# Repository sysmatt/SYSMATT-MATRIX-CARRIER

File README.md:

# SYSMATT-MATRIX-CARRIER
## An all-pcb combined ESB32 based WS2812B matrix carrier and diffuser.

### ... It's a sandwich. 

If you end up building these, please tag me on social media... @SYSMATT on X/Twitter - TY!

These cheap pre-made WS2812B flexible matrix boards are plentiful and availible on Amazon/Aliexpress/etc.  

They look great through a 1mm FR4 PCB diffuser. 

In this repo is the carrier board I created to control them with the common 30pin or 38pin ESP32 WROOM modules.  

It supports WLED easily, and even has suport for audio reactive WLED using the common 6-pin INMP441 digital microphone modules.

The boards are assembled in a sandwich,  The main electronics PCB with the ESP module, Mic module, A SN74AHCT125N used as a voltage translator, and an assortment of connector options for input/output.

The boards can be assembled "smart" (With an ESP) ... or "dumb"... where it will be chained from a smart board. 

Four ESP outputs are voltage level translated in total to allow you to create large matrix displays. 

There is also a fuse.  Because house fires are no joke. 

Designed using through hole because I have a pile of parts (Im a parts hoarder) ... And the are super easy for most people. 

I will add more here when I have time.  There are videos on the PHOTOS-VIDEOS directory.  Also on youtube:

Video link to YouTube:

https://youtube.com/shorts/75FGs6rpeio

https://youtube.com/shorts/8wDof0Con4Y

https://youtube.com/shorts/0d_V_7tXByc

https://www.youtube.com/watch?v=TLycWf7s_p8

I just use a couplle dots of silicone to hold the sandwitch together

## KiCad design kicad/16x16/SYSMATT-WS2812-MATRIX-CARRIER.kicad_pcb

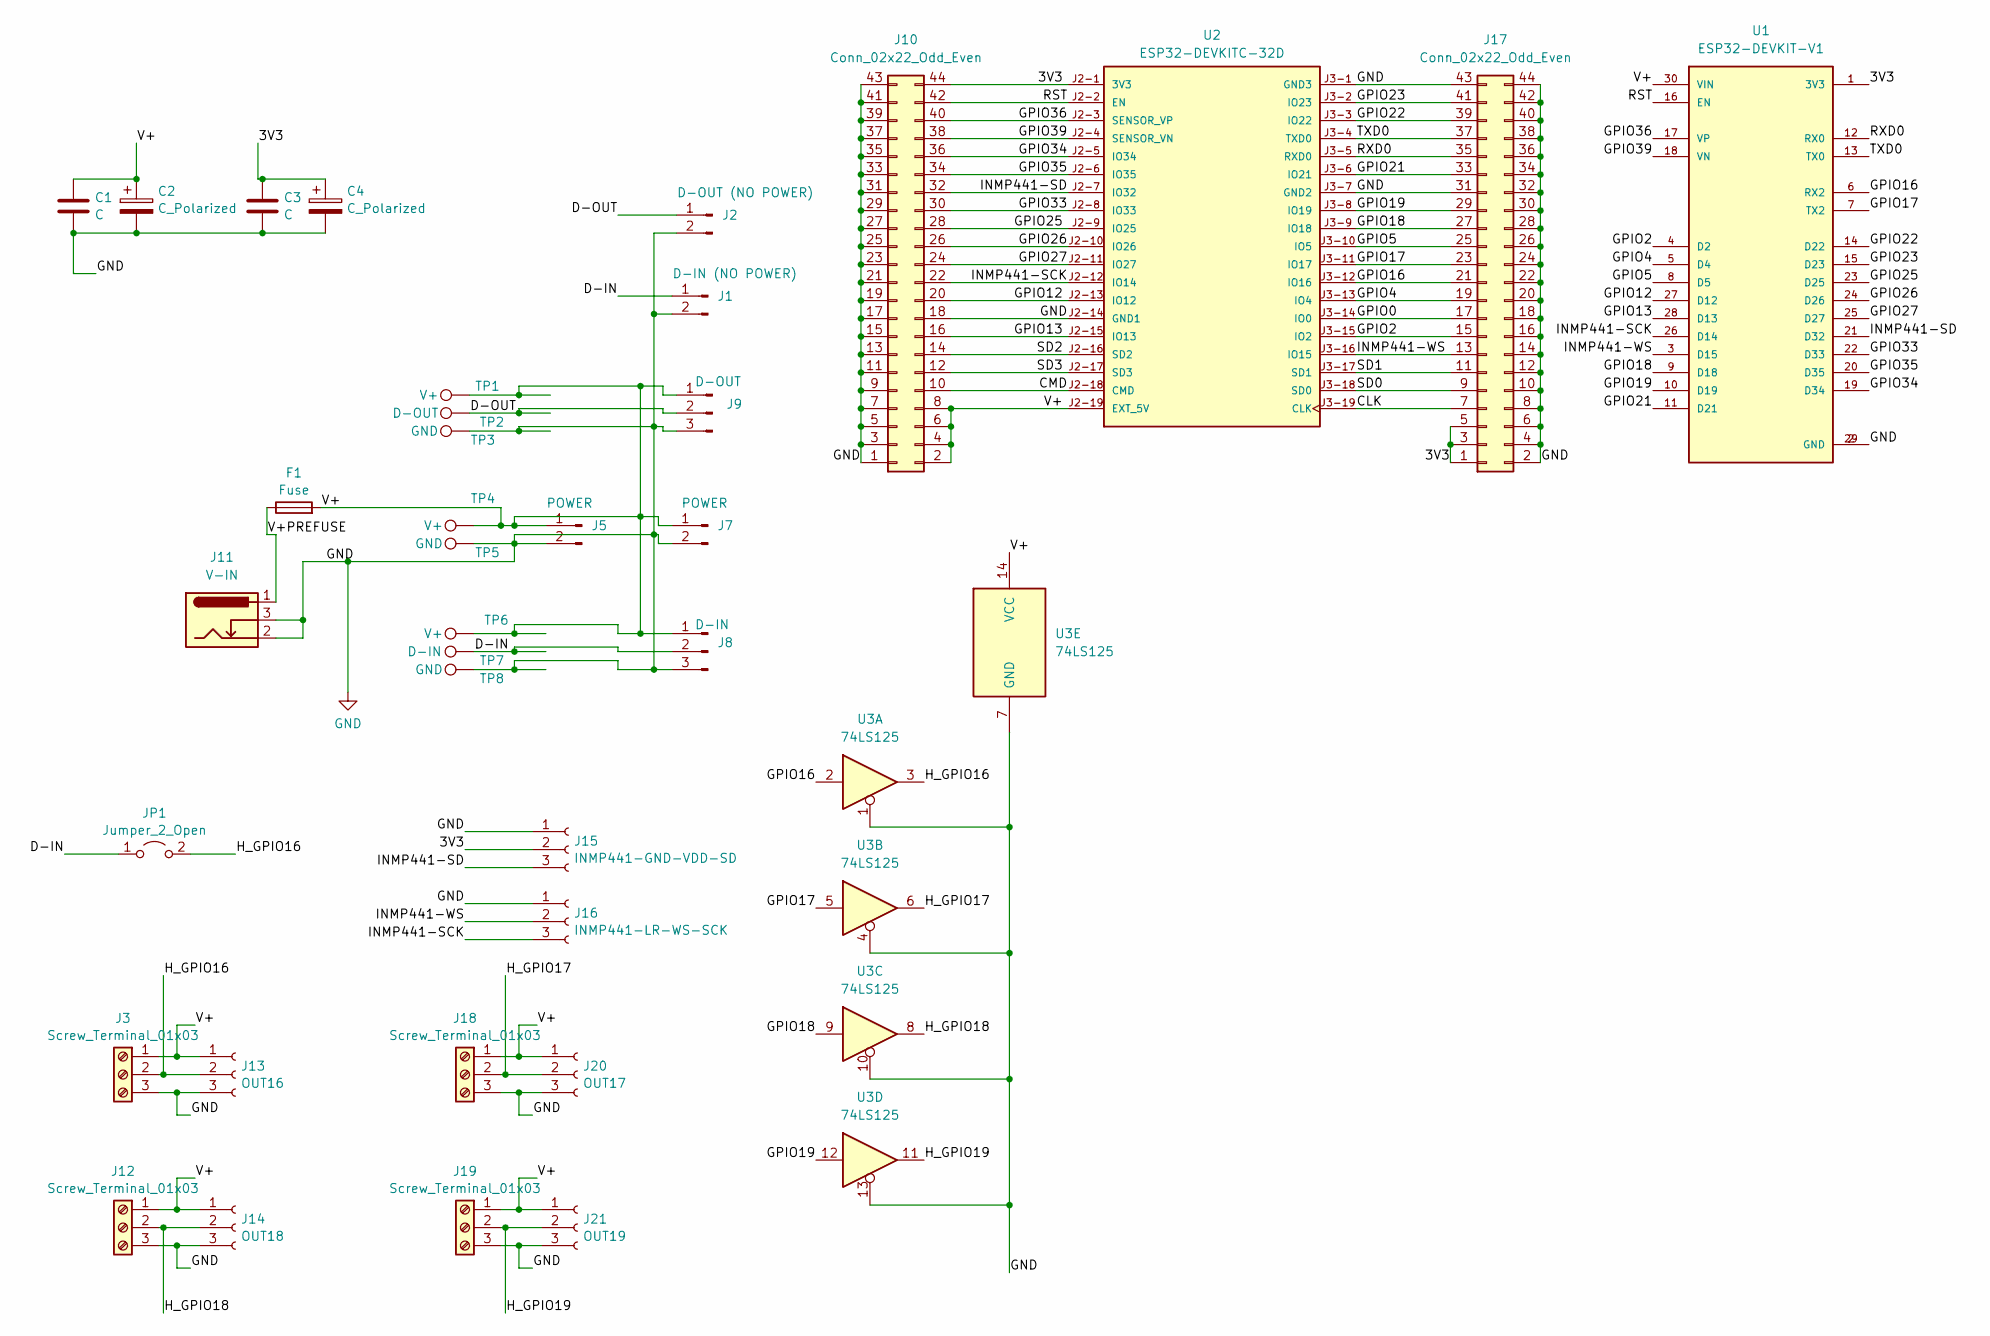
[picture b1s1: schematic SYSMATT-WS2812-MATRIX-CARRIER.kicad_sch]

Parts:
C1, C3: C; C_Disc_D3.8mm_W2.6mm_P2.50mm
C2, C4: C_Polarized; CP_Radial_D6.3mm_P2.50mm
F1: Fuse; Ebay-Fuse-holder-04mmX15mm-black-auto-fuse-dingus
J1: D-IN (NO POWER); PinHeader_1x02_P2.54mm_Horizontal
J2: D-OUT (NO POWER); PinHeader_1x02_P2.54mm_Horizontal
J3, J12, J18, J19: Screw_Terminal_01x03; TerminalBlock_bornier-3_P5.08mm
J5, J7: POWER; PinHeader_1x02_P2.54mm_Horizontal
J8: D-IN; PinHeader_1x03_P2.54mm_Horizontal
J9: D-OUT; PinHeader_1x03_P2.54mm_Horizontal
J10, J17: Conn_02x22_Odd_Even; PinSocket_2x22_P2.54mm_Vertical
J11: V-IN; BarrelJack_Horizontal
J13: OUT16; PinSocket_1x03_P2.54mm_Vertical
J14: OUT18; PinSocket_1x03_P2.54mm_Vertical
J15: INMP441-GND-VDD-SD; PinSocket_1x03_P2.54mm_Vertical
J16: INMP441-LR-WS-SCK; PinSocket_1x03_P2.54mm_Vertical
J20: OUT17; PinSocket_1x03_P2.54mm_Vertical
J21: OUT19; PinSocket_1x03_P2.54mm_Vertical
JP1: Jumper_2_Open; SolderJumper-2_P1.3mm_Open_TrianglePad1.0x1.5mm
TP1, TP4, TP6: V+; TestPoint_Pad_3.0x3.0mm
TP2: D-OUT; TestPoint_Pad_3.0x3.0mm
TP3, TP5, TP8: GND; TestPoint_Pad_3.0x3.0mm
TP7: D-IN; TestPoint_Pad_3.0x3.0mm
U1: ESP32-DEVKIT-V1; MODULE_ESP32_DEVKIT_V1-no-ant-keepout; PARTREV N/A
U2: ESP32-DEVKITC-32D; MODULE_ESP32-DEVKITC-32D-CORRECTED-WIDTH-NARROW; PARTREV V4
U3: 74LS125; DIP-14_W7.62mm_Socket_LongPads

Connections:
/3V3: C3.1, C4.1, J10.44, J15.2, J17.1, J17.3, J17.5, U1.1 (3V3), U2.J2-1 (3V3)
/CLK: J17.7, U2.J3-19 (CLK)
/CMD: J10.10, U2.J2-18 (CMD)
/D-IN: J1.1, J8.2, JP1.1 (A), TP7.1
/D-OUT: J2.1, J9.2, TP2.1
/GPIO0: J17.17, U2.J3-14 (IO0)
/GPIO2: J17.15, U1.4 (D2), U2.J3-15 (IO2)
/GPIO4: J17.19, U1.5 (D4), U2.J3-13 (IO4)
/GPIO5: J17.25, U1.8 (D5), U2.J3-10 (IO5)
/GPIO12: J10.20, U1.27 (D12), U2.J2-13 (IO12)
/GPIO13: J10.16, U1.28 (D13), U2.J2-15 (IO13)
/GPIO16: J17.21, U1.6 (RX2), U2.J3-12 (IO16), U3.2
/GPIO17: J17.23, U1.7 (TX2), U2.J3-11 (IO17), U3.5
/GPIO18: J17.27, U1.9 (D18), U2.J3-9 (IO18), U3.9
/GPIO19: J17.29, U1.10 (D19), U2.J3-8 (IO19), U3.12
/GPIO21: J17.33, U1.11 (D21), U2.J3-6 (IO21)
/GPIO22: J17.39, U1.14 (D22), U2.J3-3 (IO22)
/GPIO23: J17.41, U1.15 (D23), U2.J3-2 (IO23)
/GPIO25: J10.28, U1.23 (D25), U2.J2-9 (IO25)
/GPIO26: J10.26, U1.24 (D26), U2.J2-10 (IO26)
/GPIO27: J10.24, U1.25 (D27), U2.J2-11 (IO27)
/GPIO33: J10.30, U1.22 (D33), U2.J2-8 (IO33)
/GPIO34: J10.36, U1.19 (D34), U2.J2-5 (IO34)
/GPIO35: J10.34, U1.20 (D35), U2.J2-6 (IO35)
/GPIO36: J10.40, U1.17 (VP), U2.J2-3 (SENSOR_VP)
/GPIO39: J10.38, U1.18 (VN), U2.J2-4 (SENSOR_VN)
/H_GPIO16: J3.2, J13.2, JP1.2 (B), U3.3
/H_GPIO17: J18.2, J20.2, U3.6
/H_GPIO18: J12.2, J14.2, U3.8
/H_GPIO19: J19.2, J21.2, U3.11
/INMP441-SCK: J10.22, J16.3, U1.26 (D14), U2.J2-12 (IO14)
/INMP441-SD: J10.32, J15.3, U1.21 (D32), U2.J2-7 (IO32)
/INMP441-WS: J16.2, J17.13, U1.3 (D15), U2.J3-16 (IO15)
/RST: J10.42, U1.16 (EN), U2.J2-2 (EN)
/RXD0: J17.35, U1.12 (RX0), U2.J3-5 (RXD0)
/SD0: J17.9, U2.J3-18 (SD0)
/SD1: J17.11, U2.J3-17 (SD1)
/SD2: J10.14, U2.J2-16 (SD2)
/SD3: J10.12, U2.J2-17 (SD3)
/TXD0: J17.37, U1.13 (TX0), U2.J3-4 (TXD0)
/V+: C1.1, C2.1, F1.2, J3.1, J5.1, J7.1, J8.1, J9.1, J10.2, J10.4, J10.6, J10.8, J12.1, J13.1, J14.1, J18.1, J19.1, J20.1, J21.1, TP1.1, TP4.1, TP6.1, U1.30 (VIN), U2.J2-19 (EXT_5V), U3.14 (VCC)
/V+PREFUSE: F1.1, J11.1
GND: C1.2, C2.2, C3.2, C4.2, J1.2, J2.2, J3.3, J5.2, J7.2, J8.3, J9.3, J10.1, J10.3, J10.5, J10.7, J10.9, J10.11, J10.13, J10.15, J10.17, J10.18, J10.19, J10.21, J10.23, J10.25, J10.27, J10.29, J10.31, J10.33, J10.35, J10.37, J10.39, J10.41, J10.43, J11.2, J11.3, J12.3, J13.3, J14.3, J15.1, J16.1, J17.2, J17.4, J17.6, J17.8, J17.10, J17.12, J17.14, J17.16, J17.18, J17.20, J17.22, J17.24, J17.26, J17.28, J17.30, J17.31, J17.32, J17.34, J17.36, J17.38, J17.40, J17.42, J17.43, J17.44, J18.3, J19.3, J20.3, J21.3, TP3.1, TP5.1, TP8.1, U1.2 (GND), U1.29 (GND), U2.J2-14 (GND1), U2.J3-1 (GND3), U2.J3-7 (GND2), U3.1, U3.4, U3.7 (GND), U3.10, U3.13

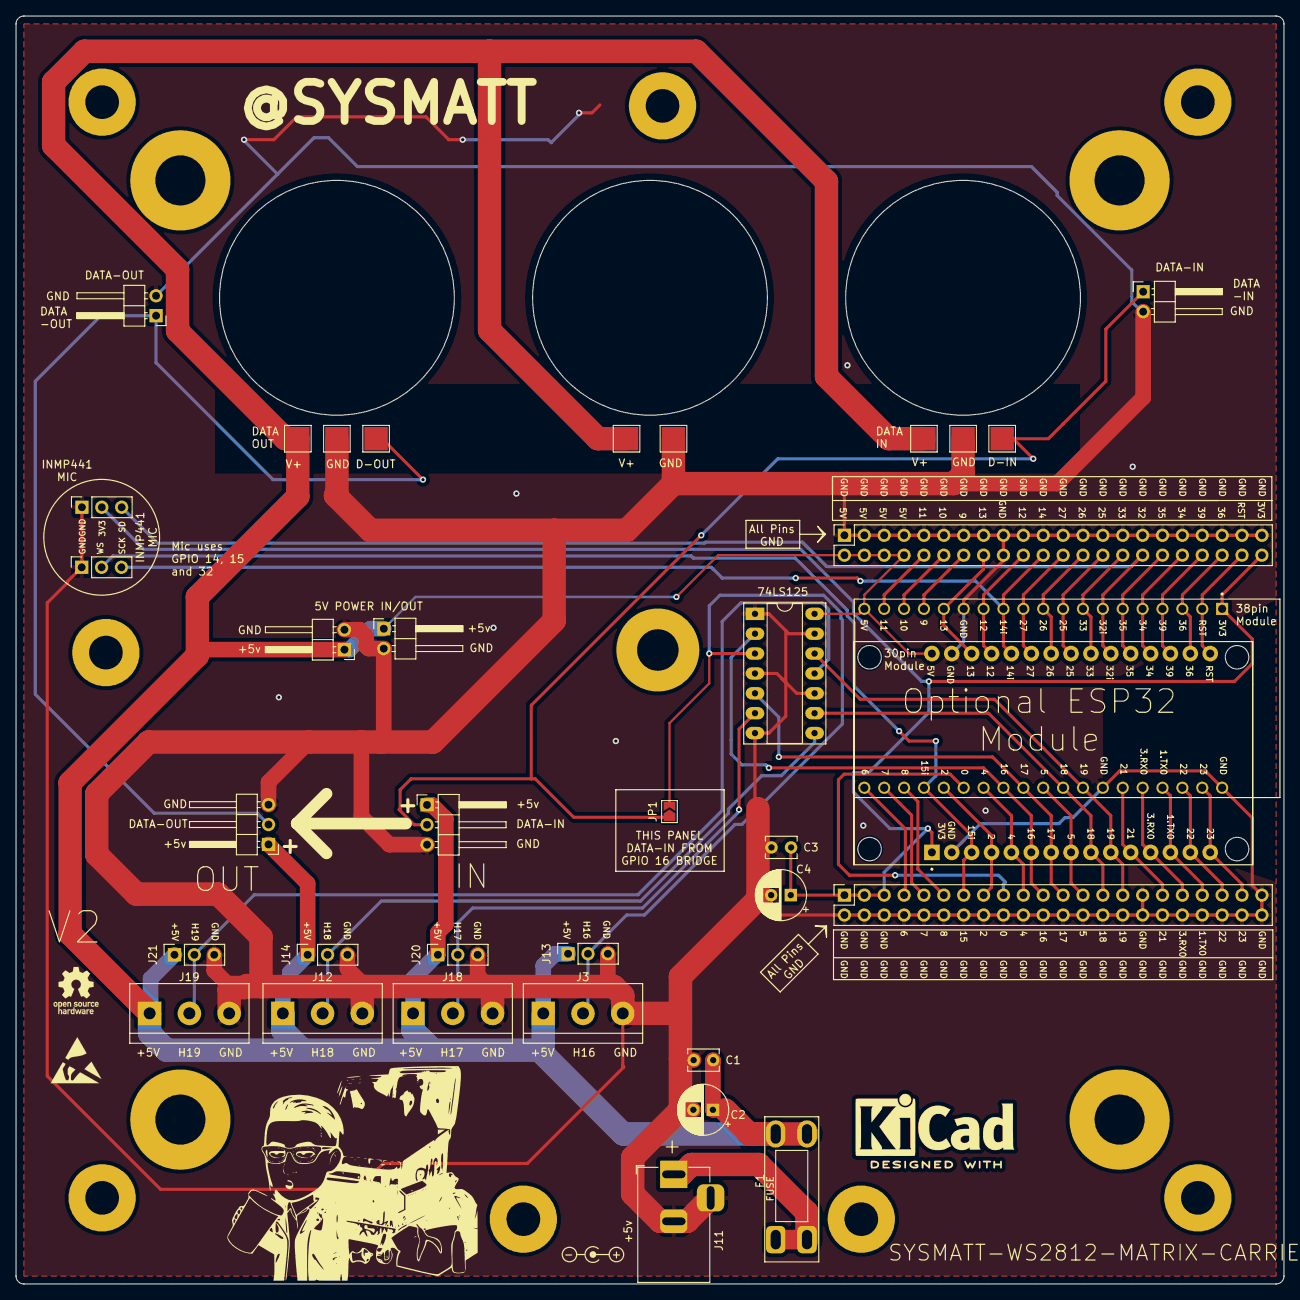
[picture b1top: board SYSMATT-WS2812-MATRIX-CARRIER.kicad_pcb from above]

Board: 2 copper layers, 162.0 x 162.0 mm, 36 parts (0 on the bottom side), 43 nets.

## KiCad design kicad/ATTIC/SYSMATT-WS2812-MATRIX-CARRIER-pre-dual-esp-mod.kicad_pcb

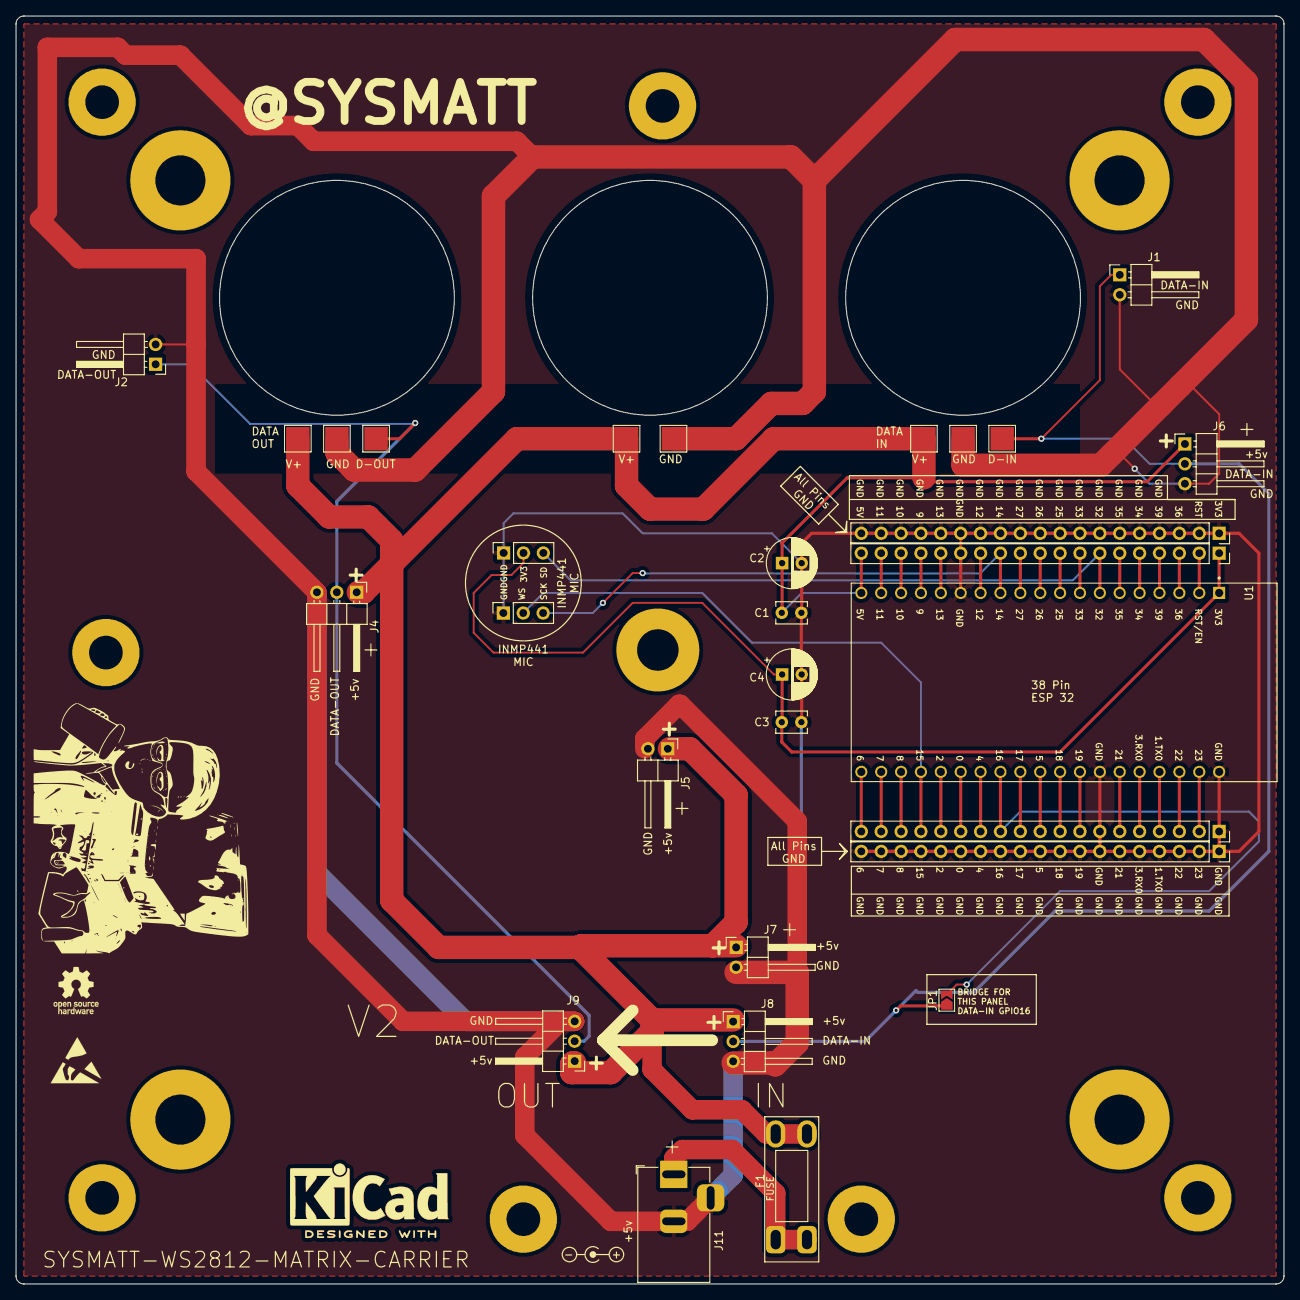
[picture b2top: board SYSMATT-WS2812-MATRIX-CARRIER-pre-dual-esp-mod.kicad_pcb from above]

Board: 2 copper layers, 162.0 x 162.0 mm, 30 parts (0 on the bottom side), 39 nets.

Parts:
C1, C3: C; C_Disc_D3.8mm_W2.6mm_P2.50mm
C2, C4: C_Polarized; CP_Radial_D6.3mm_P2.50mm
F1: Fuse; Ebay-Fuse-holder-04mmX15mm-black-auto-fuse-dingus
J1: D-IN (NO POWER); PinHeader_1x02_P2.54mm_Horizontal
J2: D-OUT (NO POWER); PinHeader_1x02_P2.54mm_Horizontal
J3, J12, J13, J14: Conn_01x19_Pin; PinSocket_1x19_P2.54mm_Vertical
J4, J9: D-OUT; PinHeader_1x03_P2.54mm_Horizontal
J5, J7: POWER; PinHeader_1x02_P2.54mm_Horizontal
J6, J8: D-IN; PinHeader_1x03_P2.54mm_Horizontal
J11: V-IN; BarrelJack_Horizontal
J15: INMP441-GND-VDD-SD; PinSocket_1x03_P2.54mm_Vertical
J16: INMP441-LR-WS-SCK; PinSocket_1x03_P2.54mm_Vertical
JP1: Jumper_2_Open; SolderJumper-2_P1.3mm_Open_TrianglePad1.0x1.5mm
TP1, TP4, TP6: V+; TestPoint_Pad_3.0x3.0mm
TP2: D-OUT; TestPoint_Pad_3.0x3.0mm
TP3, TP5, TP8: GND; TestPoint_Pad_3.0x3.0mm
TP7: D-IN; TestPoint_Pad_3.0x3.0mm
U1: ESP32-DEVKITC-32D; MODULE_ESP32-DEVKITC-32D-CORRECTED-WIDTH-NARROW

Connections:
/3V3: C3.1, C4.1, J3.1, J15.2, U1.J2-1 (3V3)
/D-IN: J1.1, J6.2, J8.2, JP1.1 (A), TP7.1
/D-OUT: J2.1, J4.2, J9.2, TP2.1
/INMP441-SCK: J3.12, J16.3, U1.J2-12 (IO14)
/INMP441-SD: J3.7, J15.3, U1.J2-7 (IO32)
/INMP441-WS: J12.16, J16.2, U1.J3-16 (IO15)
/IO16: J12.12, JP1.2 (B), U1.J3-12 (IO16)
/V+: C1.1, C2.1, F1.2, J3.19, J4.1, J5.1, J6.1, J7.1, J8.1, J9.1, TP1.1, TP4.1, TP6.1, U1.J2-19 (EXT_5V)
/V+PREFUSE: F1.1, J11.1
GND: C1.2, C2.2, C3.2, C4.2, J1.2, J2.2, J3.14, J4.3, J5.2, J6.3, J7.2, J8.3, J9.3, J11.2, J11.3, J12.1, J12.7, J13.1, J13.2, J13.3, J13.4, J13.5, J13.6, J13.7, J13.8, J13.9, J13.10, J13.11, J13.12, J13.13, J13.14, J13.15, J13.16, J13.17, J13.18, J13.19, J14.1, J14.2, J14.3, J14.4, J14.5, J14.6, J14.7, J14.8, J14.9, J14.10, J14.11, J14.12, J14.13, J14.14, J14.15, J14.16, J14.17, J14.18, J14.19, J15.1, J16.1, TP3.1, TP5.1, TP8.1, U1.J2-14 (GND1), U1.J3-1 (GND3), U1.J3-7 (GND2)
unnamed: J3.2, U1.J2-2 (EN)
unnamed: J3.3, U1.J2-3 (SENSOR_VP)
unnamed: J3.4, U1.J2-4 (SENSOR_VN)
unnamed: J3.5, U1.J2-5 (IO34)
unnamed: J3.6, U1.J2-6 (IO35)
unnamed: J3.8, U1.J2-8 (IO33)
unnamed: J3.9, U1.J2-9 (IO25)
unnamed: J3.10, U1.J2-10 (IO26)
unnamed: J3.11, U1.J2-11 (IO27)
unnamed: J3.13, U1.J2-13 (IO12)
unnamed: J3.15, U1.J2-15 (IO13)
unnamed: J3.16, U1.J2-16 (SD2)
unnamed: J3.17, U1.J2-17 (SD3)
unnamed: J3.18, U1.J2-18 (CMD)
unnamed: J12.2, U1.J3-2 (IO23)
unnamed: J12.3, U1.J3-3 (IO22)
unnamed: J12.4, U1.J3-4 (TXD0)
unnamed: J12.5, U1.J3-5 (RXD0)
unnamed: J12.6, U1.J3-6 (IO21)
unnamed: J12.8, U1.J3-8 (IO19)
unnamed: J12.9, U1.J3-9 (IO18)
unnamed: J12.10, U1.J3-10 (IO5)
unnamed: J12.11, U1.J3-11 (IO17)
unnamed: J12.13, U1.J3-13 (IO4)
unnamed: J12.14, U1.J3-14 (IO0)
unnamed: J12.15, U1.J3-15 (IO2)
unnamed: J12.17, U1.J3-17 (SD1)
unnamed: J12.18, U1.J3-18 (SD0)
unnamed: J12.19, U1.J3-19 (CLK)

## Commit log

2024-02-17 initial public commit
2024-03-10 Update README.md
    soc media tag
